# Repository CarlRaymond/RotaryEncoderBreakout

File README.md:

A breakout board for SparkFun's *Rotary Encoder - Illuminated (RGB)*
https://www.sparkfun.com/products/10982 (mfg. part number seems to be EC12PLRGB). The part includes an RGB LED, which is controlled by a WS2811 driver on the board. This turns it into an individually addressable RGB LED that can be part of a chain. See Adafruit's [The Magic of NeoPixels](https://learn.adafruit.com/adafruit-neopixel-uberguide/the-magic-of-neopixels?view=all).

The board can be used as an Arduino Uno shield, or on a breadboard. An extra header on the top brings out the data in and out lines, and allows selecting the WS2811 bitrate (either 400KHz or 800KHz). When used with an Arduino, the data in can come from pin PC3, or through the top side header. This lets it be used at the beginning, middle, or end of a chain of pixels.

Designed with KiCad. Includes sample Arduino code.

Bare board can be ordered from OSH Park: 
https://oshpark.com/shared_projects/EhRHmfJX

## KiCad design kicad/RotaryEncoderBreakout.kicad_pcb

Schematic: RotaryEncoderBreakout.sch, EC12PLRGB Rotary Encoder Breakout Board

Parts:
C1, C2, C3, C4: .1uF; C_0805_HandSoldering
J1, J2: Conn_01x04_Male; Socket_Strip_Straight_1x04_Pitch2.54mm
J3: Conn_01x05_Male; Pin_Header_Straight_1x05_Pitch2.54mm
R1, R4, R5: 10K; R_0805_HandSoldering
R2, R3, R8: 22K; R_0805_HandSoldering
R6: 100; R_0805_HandSoldering
R7: 33; R_0805_HandSoldering
SW1: EC12PLRGB; EC12PLRGB_Rotary_Encoder
U1: WS2811; SOIC-8_3.9x4.9mm_Pitch1.27mm

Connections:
+5V: J2.4, J3.5, R4.1, R5.1, R6.1, SW1.5
GND: C1.2, C2.2, C3.1, C4.2, J2.2, J2.3, R1.2, SW1.C, U1.4 (GND)
unnamed: C1.1, J1.3, R2.2
unnamed: C2.1, J1.2, R3.2
unnamed: C3.2, R6.2, U1.8 (VDD)
unnamed: C4.1, J1.4, R8.2
unnamed: J1.1, J3.1
unnamed: J3.2, R7.2
unnamed: J3.3, U1.5 (DOUT)
unnamed: J3.4, U1.7 (SET)
unnamed: R1.1, R8.1, SW1.3
unnamed: R2.1, R5.2, SW1.A
unnamed: R3.1, R4.2, SW1.B
unnamed: R7.1, U1.6 (DIN)
unnamed: SW1.1, U1.1 (OUTR)
unnamed: SW1.2, U1.2 (OUTG)
unnamed: SW1.4, U1.3 (OUTB)

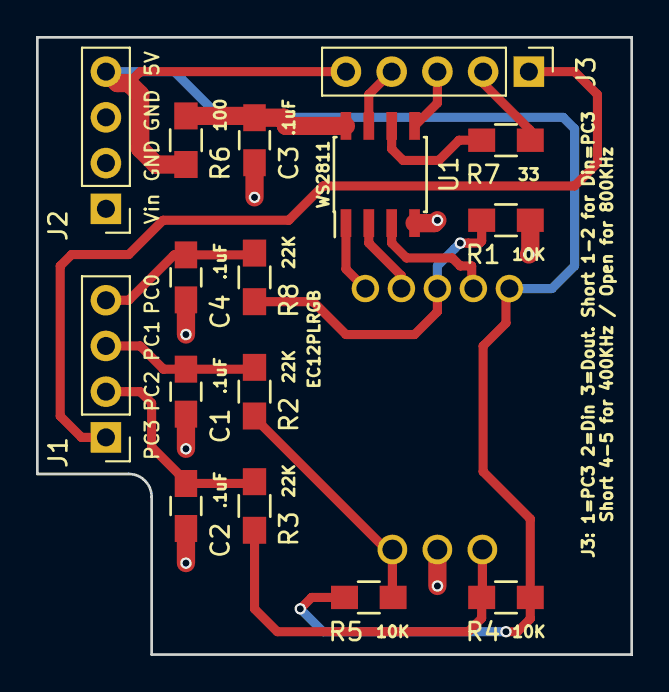
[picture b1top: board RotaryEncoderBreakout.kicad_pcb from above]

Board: 2 copper layers, 33.0 x 34.3 mm, 17 parts (0 on the bottom side), 17 nets.

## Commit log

2017-12-07 Initial checkin
2017-12-07 Layout complete
2017-12-07 Better silkscreen
2017-12-08 Final layout
2017-12-11 Created local symbol and footprint libraries for portability
2017-12-11 Changed symbol and library references to local copy
2017-12-13 Add README.md
2017-12-13 Moved README.md to right place
2017-12-13 Fix image path in README.md
2017-12-13 Add more detail to README.md.
2017-12-15 Add image of schematic.
2017-12-16 Silkscreen refinement
2017-12-16 Update 3D render
2017-12-16 Update 3D render again
2017-12-30 Update component values
2017-12-30 Added Arduino code
2017-12-31 Final design
    Add Arduino code, datasheets, and update gerber/pdf/dxf/image output.
2017-12-31 Fix image path.
2017-12-31 Update schematic image
2018-01-01 Add bill of materials
2018-01-01 Add OSHPark URL
2018-01-01 Fixed link to OSH Park project.
2018-02-09 Change J1 and J2 to socket headers
    Change J1 & J2 from pin headers to Arduino-style socket strips.
2018-02-09 Replace pin headers with socket strips
